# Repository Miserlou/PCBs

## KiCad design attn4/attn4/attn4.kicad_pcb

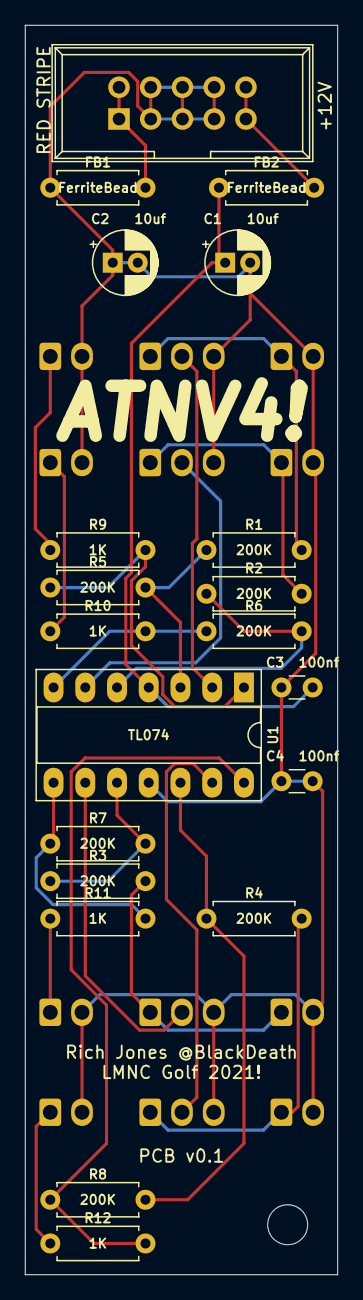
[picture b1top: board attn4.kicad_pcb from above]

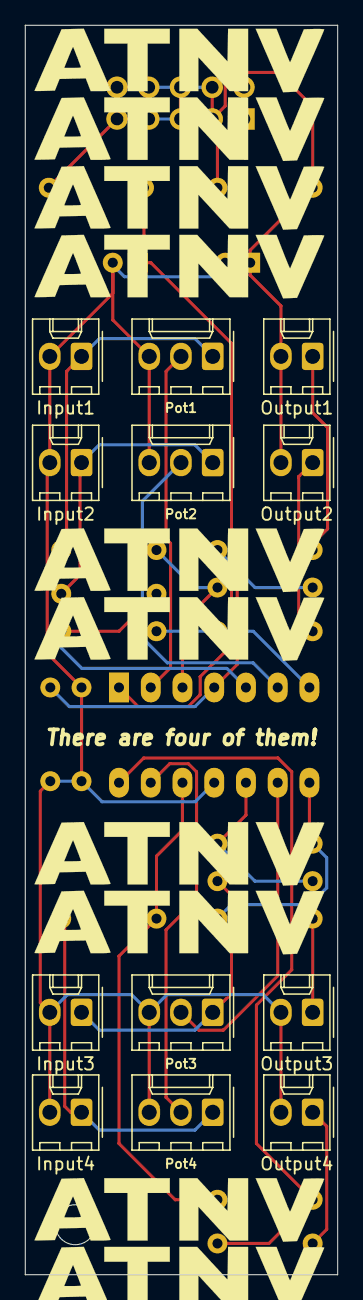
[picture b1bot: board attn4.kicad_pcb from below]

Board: 2 copper layers, 25.0 x 100.0 mm, 33 parts (12 on the bottom side), 24 nets.

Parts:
C1, C2: 10uf; CP_Radial_D5.0mm_P2.00mm
C3, C4: 100nf; C_Disc_D3.0mm_W1.6mm_P2.50mm
FB1, FB2: FerriteBead; R_Axial_DIN0207_L6.3mm_D2.5mm_P7.62mm_Horizontal
H1: MountingHole; MountingHole_3.2mm_M3
Input1: Input1; Molex_KK-254_AE-6410-02A_1x02_P2.54mm_Vertical
Input2: Input2; Molex_KK-254_AE-6410-02A_1x02_P2.54mm_Vertical
Input3: Input3; Molex_KK-254_AE-6410-02A_1x02_P2.54mm_Vertical
Input4: Input4; Molex_KK-254_AE-6410-02A_1x02_P2.54mm_Vertical
J5: Synth_power_2x5; Power_Header
Output1: Output1; Molex_KK-254_AE-6410-02A_1x02_P2.54mm_Vertical
Output2: Output2; Molex_KK-254_AE-6410-02A_1x02_P2.54mm_Vertical
Output3: Output3; Molex_KK-254_AE-6410-02A_1x02_P2.54mm_Vertical
Output4: Output4; Molex_KK-254_AE-6410-02A_1x02_P2.54mm_Vertical
Pot1, Pot2, Pot3, Pot4: 100K; Molex_KK-254_AE-6410-03A_1x03_P2.54mm_Vertical
R1, R2, R3, R4, R5, R6, R7, R8: 200K; R_Axial_DIN0207_L6.3mm_D2.5mm_P7.62mm_Horizontal
R9, R10, R11, R12: 1K; R_Axial_DIN0207_L6.3mm_D2.5mm_P7.62mm_Horizontal
U1: TL074; DIP-14_W7.62mm_Socket_LongPads

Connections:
GND: C1.2, C2.1, C2.2, C3.1, C4.1, C4.2, FB1.1, Input1.2, Input2.2, Input3.2, Input4.2, J5.3, J5.4, J5.5, J5.6, J5.7, J5.8, Output1.2, Output2.2, Output3.2, Output4.2, Pot1.3, Pot2.3, Pot3.3, Pot4.3, U1.11
unnamed: C1.1, C3.2, FB2.1, U1.4
unnamed: FB1.2, J5.1, J5.2
unnamed: FB2.2, J5.9, J5.10
unnamed: Input1.1, Pot1.1, R1.2
unnamed: Input2.1, Pot2.1, R2.2
unnamed: Input3.1, Pot3.1, R3.2
unnamed: Input4.1, Pot4.1, R4.2
unnamed: Output1.1, R9.1
unnamed: Output2.1, R10.1
unnamed: Output3.1, R11.1
unnamed: Output4.1, R12.1
unnamed: Pot1.2, U1.2
unnamed: Pot2.2, U1.6
unnamed: Pot3.2, U1.9
unnamed: Pot4.2, U1.13
unnamed: R1.1, R5.2, U1.3
unnamed: R2.1, R6.2, U1.5
unnamed: R3.1, R7.2, U1.10
unnamed: R4.1, R8.2, U1.12
unnamed: R5.1, R9.2, U1.1
unnamed: R6.1, R10.2, U1.7
unnamed: R7.1, R11.2, U1.8
unnamed: R8.1, R12.2, U1.14

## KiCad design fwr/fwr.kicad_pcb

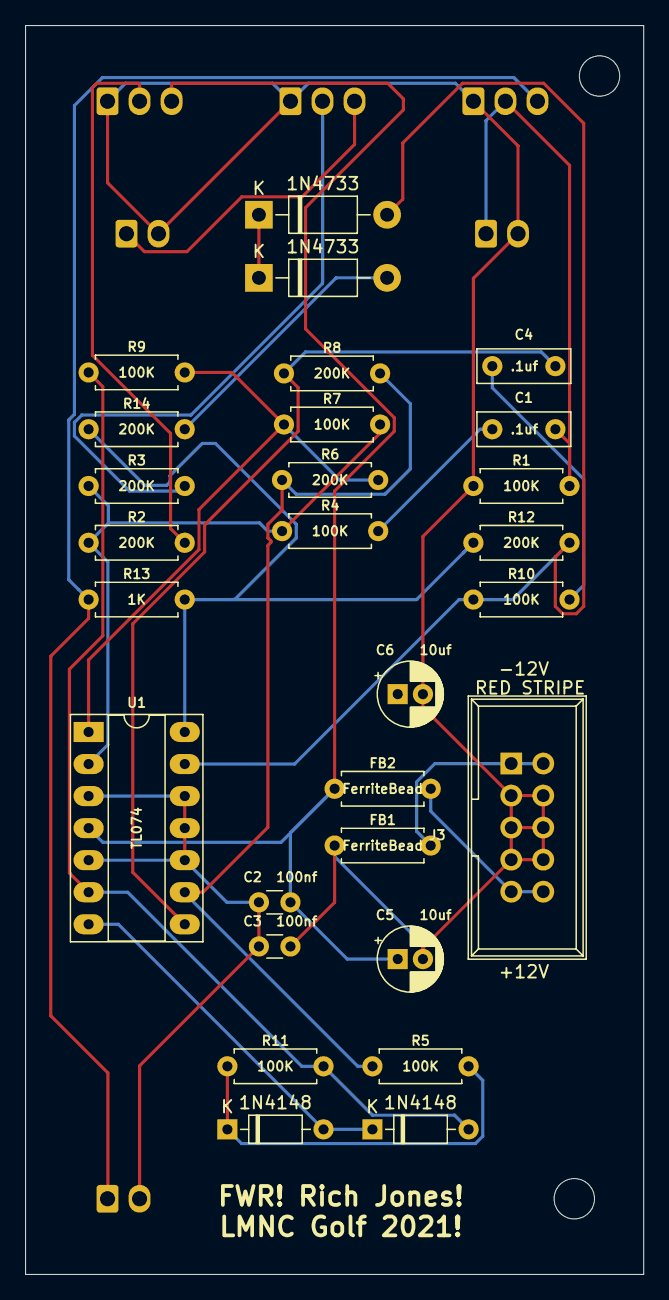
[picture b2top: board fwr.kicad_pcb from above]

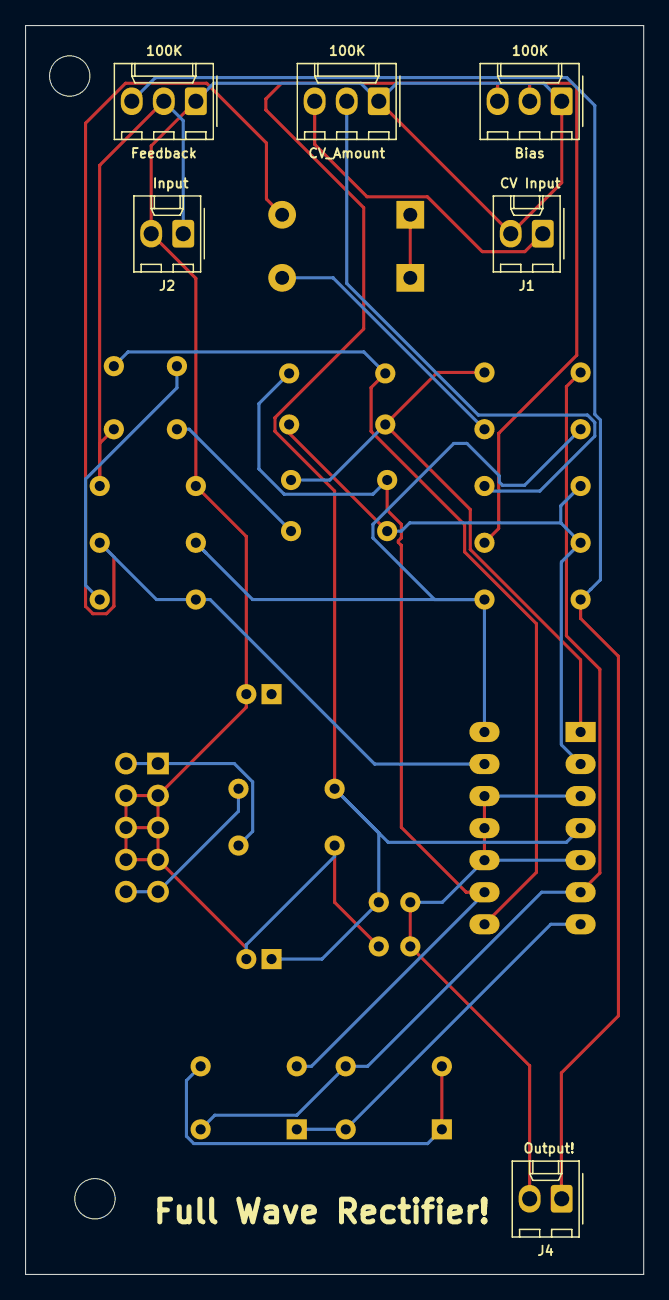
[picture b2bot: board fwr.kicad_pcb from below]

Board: 2 copper layers, 49.0 x 99.0 mm, 36 parts (6 on the bottom side), 22 nets.

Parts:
1N4148, 1N4148#2: 1N4148; D_DO-35_SOD27_P7.62mm_Horizontal
1N4733, 1N4733#2: 1N4733; D_DO-41_SOD81_P10.16mm_Horizontal
 : MountingHole; MountingHole_3.2mm_M3
Bias: 100K; Molex_KK-254_AE-6410-03A_1x03_P2.54mm_Vertical
C1, C4: .1uf; C_Rect_L7.2mm_W2.5mm_P5.00mm_FKS2_FKP2_MKS2_MKP2
C2, C3: 100nf; C_Disc_D3.0mm_W1.6mm_P2.50mm
C5, C6: 10uf; CP_Radial_D5.0mm_P2.00mm
CV_Amount: 100K; Molex_KK-254_AE-6410-03A_1x03_P2.54mm_Vertical
FB1, FB2: FerriteBead; R_Axial_DIN0207_L6.3mm_D2.5mm_P7.62mm_Horizontal
Feedback: 100K; Molex_KK-254_AE-6410-03A_1x03_P2.54mm_Vertical
H1: MountingHole; MountingHole_3.2mm_M3
J1: CV_Input; Molex_KK-254_AE-6410-02A_1x02_P2.54mm_Vertical
J2: Input; Molex_KK-254_AE-6410-02A_1x02_P2.54mm_Vertical
J3: Synth_power_2x5; Power_Header
J4: Output; Molex_KK-254_AE-6410-02A_1x02_P2.54mm_Vertical
R1, R4, R5, R7, R9, R10, R11: 100K; R_Axial_DIN0207_L6.3mm_D2.5mm_P7.62mm_Horizontal
R2, R3, R6, R8, R12, R14: 200K; R_Axial_DIN0207_L6.3mm_D2.5mm_P7.62mm_Horizontal
R13: 1K; R_Axial_DIN0207_L6.3mm_D2.5mm_P7.62mm_Horizontal
U1: TL074; DIP-14_W7.62mm_Socket_LongPads

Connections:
+12V: Bias.3, C2.2, C5.1, FB2.1, U1.4
-12V: Bias.1, C2.1, C3.1, C3.2, C5.2, C6.1, C6.2, CV_Amount.1, FB1.1, Feedback.1, J1.2, J2.2, J3.3, J3.4, J3.5, J3.6, J3.7, J3.8, J4.2, R1.1, U1.3, U1.5, U1.10, U1.11, U1.12
unnamed: Bias.2, R2.2
unnamed: C1.1, R4.2
unnamed: C1.2, Feedback.2, J2.1, R1.2
unnamed: C4.1, R10.2
unnamed: C4.2, R8.1, U1.8
unnamed: CV_Amount.2, R3.2
unnamed: CV_Amount.3, J1.1
unnamed: 1N4148.1, 1N4148#2.2, U1.7
unnamed: 1N4148.2, R9.1, R11.2, U1.6
unnamed: 1N4148#2.1, R5.2, R11.1
unnamed: 1N4733.1, 1N4733#2.1
unnamed: 1N4733.2, R10.1, R12.2, U1.13
unnamed: 1N4733#2.2, R14.2
unnamed: FB1.2, J3.1, J3.2
unnamed: FB2.2, J3.9, J3.10
unnamed: Feedback.3, J4.1, R13.1
unnamed: R2.1, R3.1, R4.1, R7.2, U1.2
unnamed: R5.1, R6.1, R8.2, U1.9
unnamed: R6.2, R7.1, R9.2, U1.1
unnamed: R12.1, R13.2, R14.1, U1.14

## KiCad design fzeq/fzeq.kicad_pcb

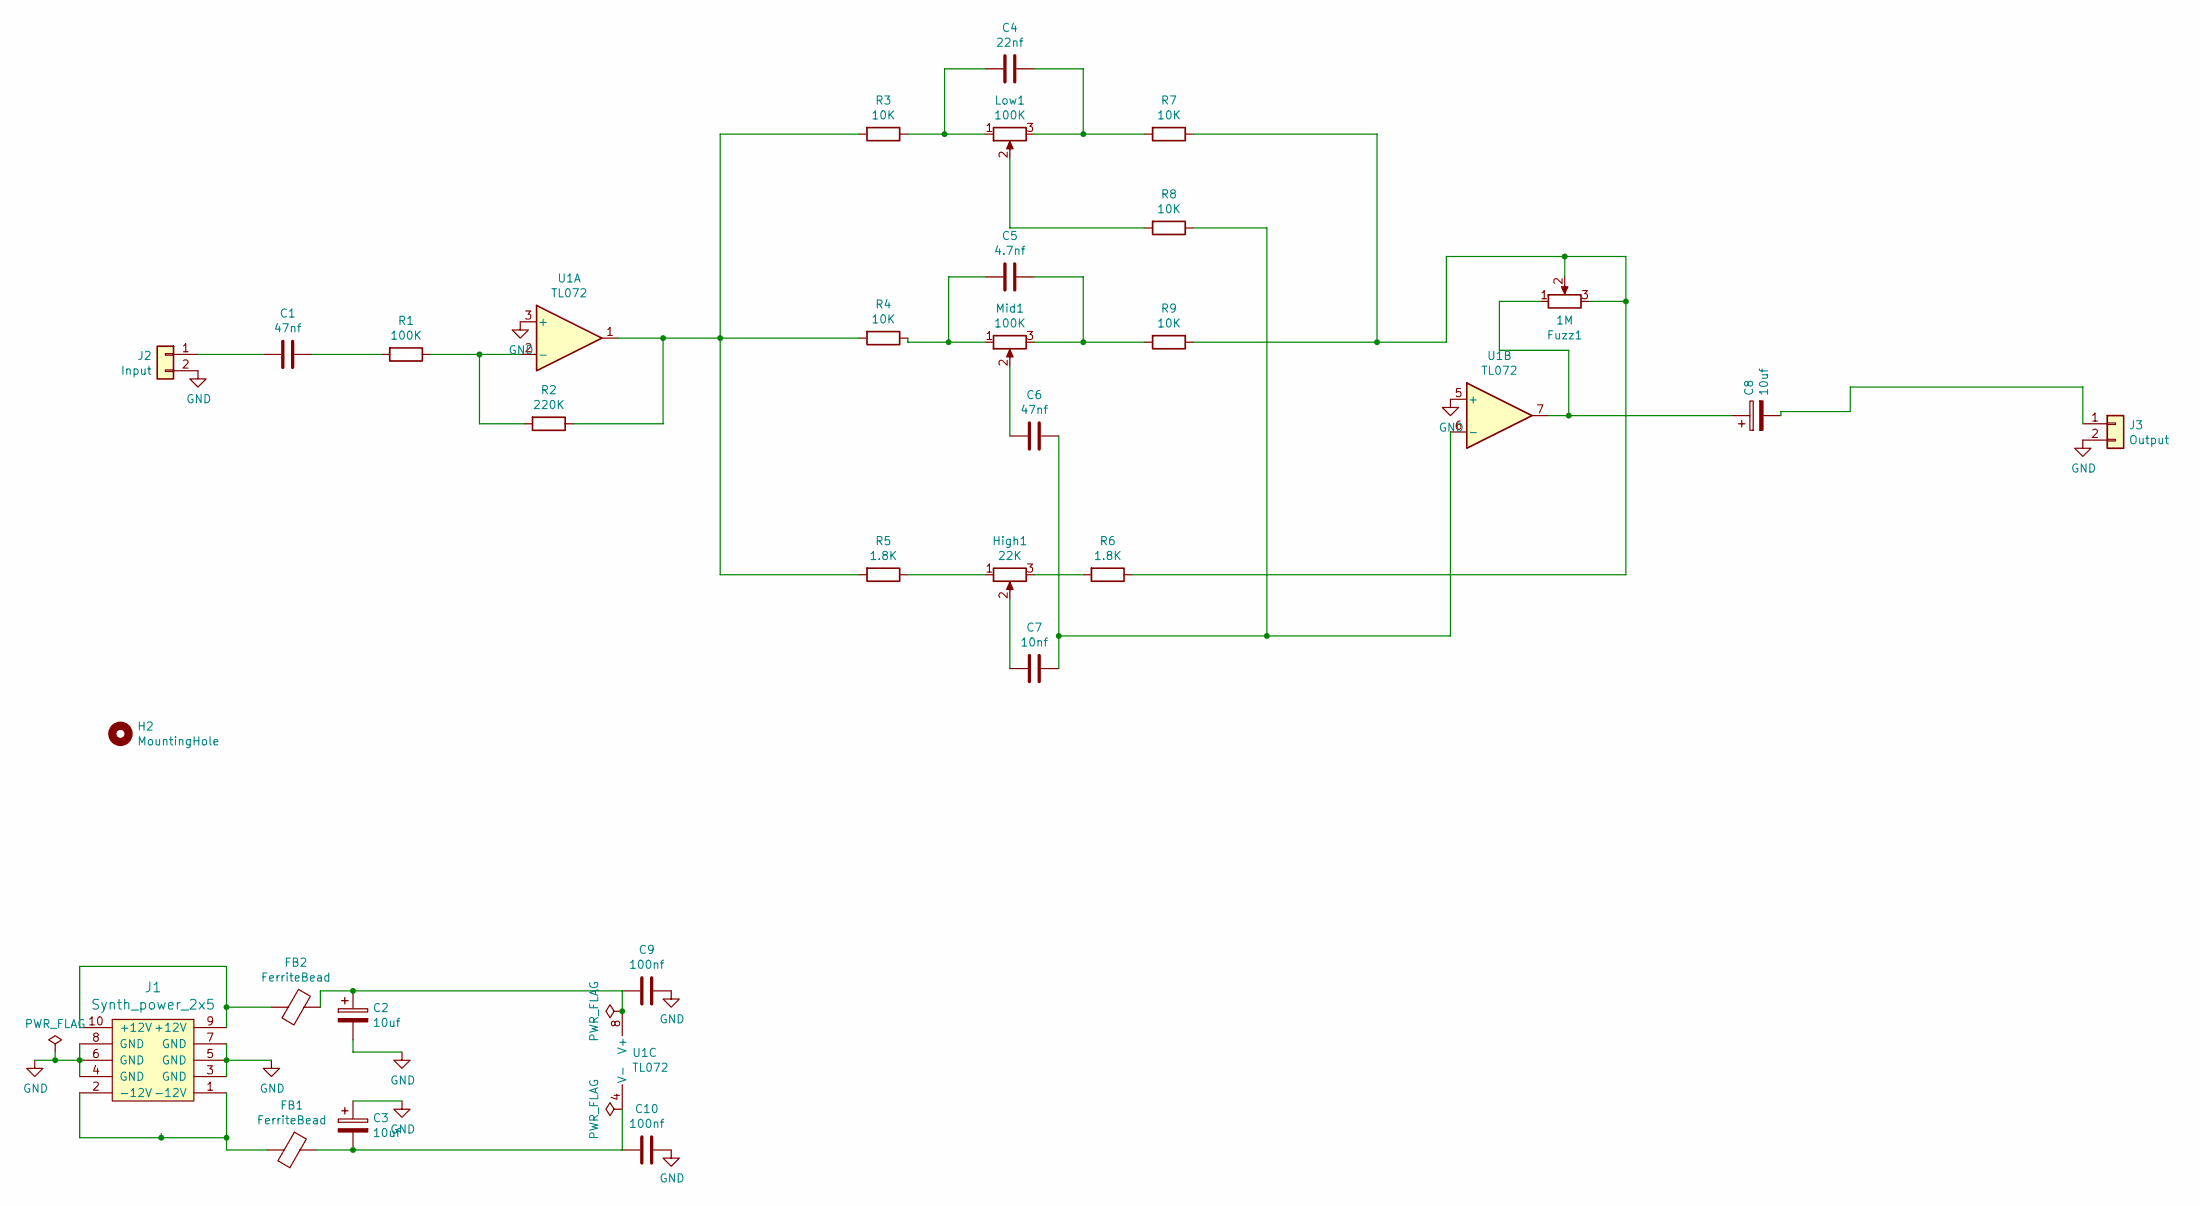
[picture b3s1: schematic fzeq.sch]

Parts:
C1, C6: 47nf; C_Disc_D3.0mm_W1.6mm_P2.50mm
C2, C3, C8: 10uf; CP_Radial_D5.0mm_P2.00mm
C4: 22nf; C_Disc_D3.0mm_W1.6mm_P2.50mm
C5: 4.7nf; C_Disc_D3.0mm_W1.6mm_P2.50mm
C7: 10nf; C_Disc_D3.0mm_W1.6mm_P2.50mm
C9, C10: 100nf; C_Disc_D3.0mm_W1.6mm_P2.50mm
FB1, FB2: FerriteBead; R_Axial_DIN0207_L6.3mm_D2.5mm_P7.62mm_Horizontal
Fuzz1: 1M; Molex_KK-254_AE-6410-03A_1x03_P2.54mm_Vertical
H2: MountingHole; MountingHole_3.2mm_M3
High1: 22K; Molex_KK-254_AE-6410-03A_1x03_P2.54mm_Vertical
J1: Synth_power_2x5; Power_Header
J2: Input; Molex_KK-254_AE-6410-02A_1x02_P2.54mm_Vertical
J3: Output; Molex_KK-254_AE-6410-02A_1x02_P2.54mm_Vertical
Low1: 100K; Molex_KK-254_AE-6410-03A_1x03_P2.54mm_Vertical
Mid1: 100K; Molex_KK-254_AE-6410-03A_1x03_P2.54mm_Vertical
R1: 100K; R_Axial_DIN0207_L6.3mm_D2.5mm_P7.62mm_Horizontal
R2: 220K; R_Axial_DIN0207_L6.3mm_D2.5mm_P7.62mm_Horizontal
R3, R4, R7, R8, R9: 10K; R_Axial_DIN0207_L6.3mm_D2.5mm_P7.62mm_Horizontal
R5, R6: 1.8K; R_Axial_DIN0207_L6.3mm_D2.5mm_P7.62mm_Horizontal
U1: TL072; DIP-8_W7.62mm_Socket_LongPads

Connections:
GND: C2.2, C3.1, C9.1, C10.1, J1.3 (GND), J1.4 (GND), J1.5 (GND), J1.6 (GND), J1.7 (GND), J1.8 (GND), J2.2, J3.2, U1.3 (+), U1.5 (+)
unnamed: C1.1, R1.2
unnamed: C1.2, J2.1
unnamed: C2.1, C9.2, FB2.1, U1.8 (V+)
unnamed: C4.1, Low1.3, R7.2
unnamed: C4.2, Low1.1, R3.1
unnamed: C5.1, Mid1.3, R9.2
unnamed: C5.2, Mid1.1, R4.1
unnamed: C6.1, C7.1, R8.1, U1.6 (-)
unnamed: C6.2, Mid1.2
unnamed: C7.2, High1.2
unnamed: C8.1, Fuzz1.1, U1.7
unnamed: C8.2, J3.1
unnamed: C3.2, C10.2, FB1.1, U1.4 (V-)
unnamed: FB1.2, J1.1 (-12V), J1.2 (-12V)
unnamed: FB2.2, J1.9 (+12V), J1.10 (+12V)
unnamed: Fuzz1.2, Fuzz1.3, R6.1, R7.1, R9.1
unnamed: High1.1, R5.1
unnamed: High1.3, R6.2
unnamed: Low1.2, R8.2
unnamed: R1.1, R2.2, U1.2 (-)
unnamed: R2.1, R3.2, R4.2, R5.2, U1.1

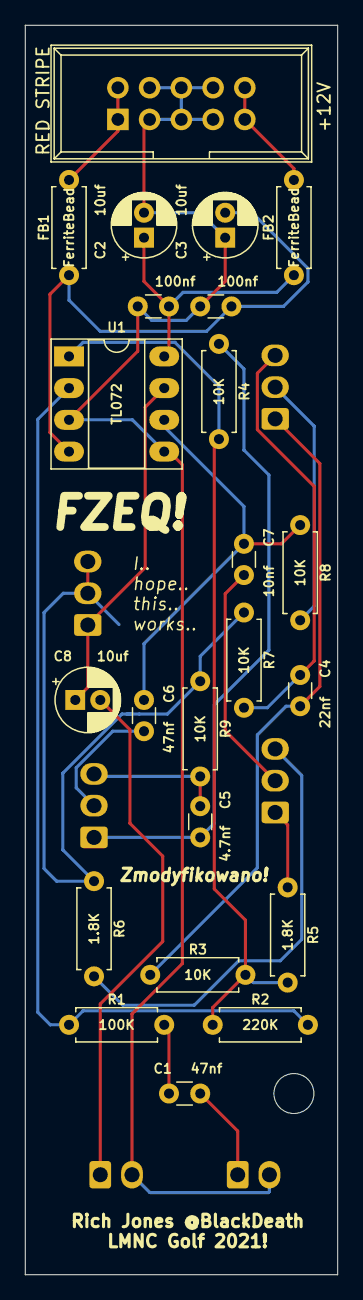
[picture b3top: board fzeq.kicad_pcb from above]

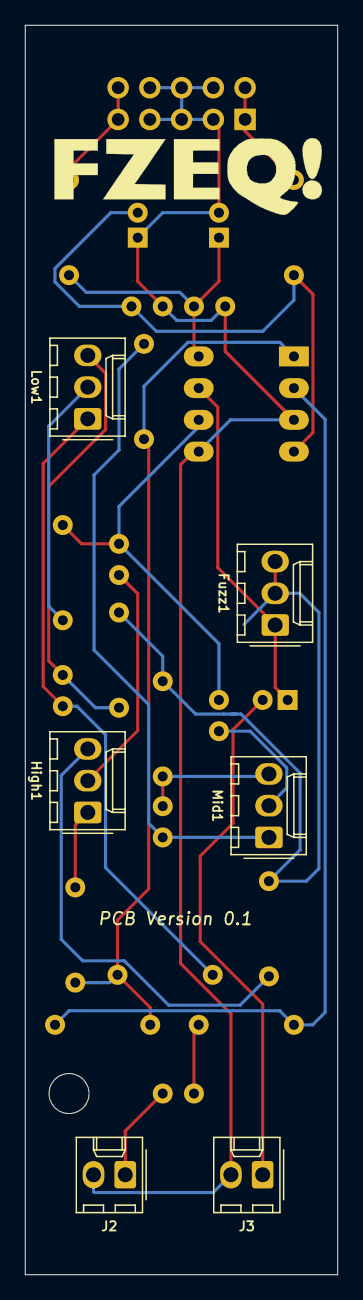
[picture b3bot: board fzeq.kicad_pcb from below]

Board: 2 copper layers, 25.0 x 100.0 mm, 30 parts (6 on the bottom side), 22 nets.

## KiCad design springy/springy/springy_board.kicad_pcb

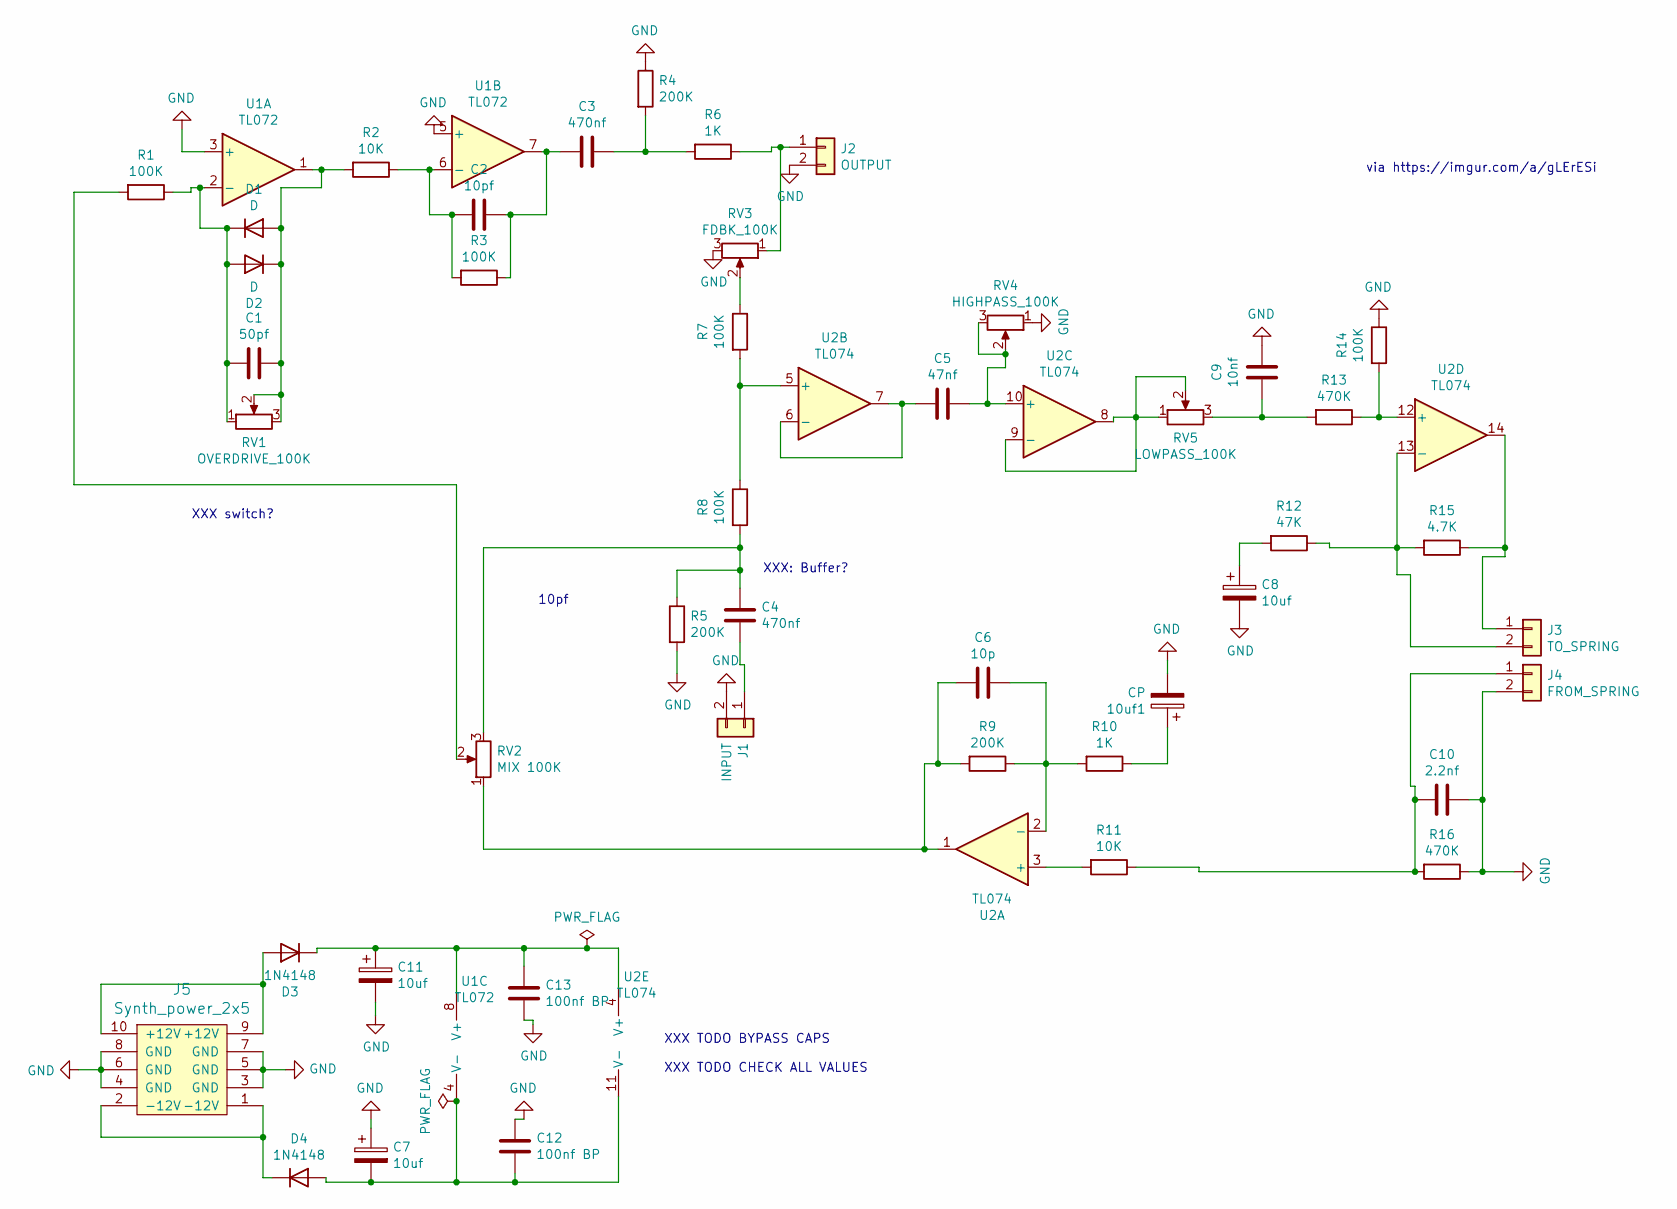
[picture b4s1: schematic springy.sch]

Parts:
10uf1: CP; CP_Radial_D6.3mm_P2.50mm
C1: 50pf; C_Disc_D3.0mm_W1.6mm_P2.50mm
C2: 10pf; C_Disc_D3.0mm_W1.6mm_P2.50mm
C3, C4: 470nf; C_Disc_D3.0mm_W1.6mm_P2.50mm
C5: 47nf; C_Disc_D3.0mm_W1.6mm_P2.50mm
C6: 10p; C_Disc_D3.0mm_W1.6mm_P2.50mm
C7, C8, C11: 10uf; CP_Radial_D6.3mm_P2.50mm
C9: 10nf; C_Disc_D3.0mm_W1.6mm_P2.50mm
C10: 2.2nf; C_Disc_D3.0mm_W1.6mm_P2.50mm
C12, C13: 100nf BP; C_Disc_D3.0mm_W1.6mm_P2.50mm
D1, D2: D; D_DO-41_SOD81_P7.62mm_Horizontal
D3, D4: 1N4148; D_DO-35_SOD27_P7.62mm_Horizontal
J1: INPUT; Molex_KK-254_AE-6410-02A_1x02_P2.54mm_Vertical
J2: OUTPUT; Molex_KK-254_AE-6410-02A_1x02_P2.54mm_Vertical
J3: TO_SPRING; Molex_KK-254_AE-6410-02A_1x02_P2.54mm_Vertical
J4: FROM_SPRING; Molex_KK-254_AE-6410-02A_1x02_P2.54mm_Vertical
J5: Synth_power_2x5; Power_Header
R1, R3, R7, R8, R14: 100K; R_Axial_DIN0207_L6.3mm_D2.5mm_P10.16mm_Horizontal
R2, R11: 10K; R_Axial_DIN0207_L6.3mm_D2.5mm_P10.16mm_Horizontal
R4, R5, R9: 200K; R_Axial_DIN0207_L6.3mm_D2.5mm_P10.16mm_Horizontal
R6, R10: 1K; R_Axial_DIN0207_L6.3mm_D2.5mm_P10.16mm_Horizontal
R12: 47K; R_Axial_DIN0207_L6.3mm_D2.5mm_P10.16mm_Horizontal
R13, R16: 470K; R_Axial_DIN0207_L6.3mm_D2.5mm_P10.16mm_Horizontal
R15: 4.7K; R_Axial_DIN0207_L6.3mm_D2.5mm_P10.16mm_Horizontal
RV1: OVERDRIVE_100K; Potentiometer_Alpha_RD901F-40-00D_Single_Vertical_CircularH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
RV2: MIX 100K; Potentiometer_Alpha_RD901F-40-00D_Single_Vertical_CircularH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
RV3: FDBK_100K; Potentiometer_Alpha_RD901F-40-00D_Single_Vertical_CircularH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
RV4: HIGHPASS_100K; Potentiometer_Alpha_RD901F-40-00D_Single_Vertical_CircularH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
RV5: LOWPASS_100K; Potentiometer_Alpha_RD901F-40-00D_Single_Vertical_CircularH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
U1: TL072; DIP-8_W7.62mm_Socket_LongPads
U2: TL074; DIP-16_W7.62mm_Socket_LongPads

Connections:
GND: 10uf1.2, C7.1, C8.2, C9.2, C10.2, C11.2, C12.1, C13.2, J1.2, J2.2, J4.2, J5.3 (GND), J5.4 (GND), J5.5 (GND), J5.6 (GND), J5.7 (GND), J5.8 (GND), R4.1, R5.2, R14.1, R16.1, RV3.3, RV4.1, U1.3 (+), U1.5 (+); also elsewhere on the board
unnamed: 10uf1.1, R10.1
unnamed: C1.1, D1.1 (K), D2.2 (A), R1.1, RV1.1, U1.2 (-)
unnamed: C1.2, D1.2 (A), D2.1 (K), R2.2, RV1.2, RV1.3, U1.1
unnamed: C2.1, R2.1, R3.2, U1.6 (-)
unnamed: C2.2, C3.1, R3.1, U1.7
unnamed: C3.2, R4.2, R6.2
unnamed: C4.1, R5.1, R8.2, RV2.3
unnamed 8: C4.2, J1.1; also elsewhere on the board
unnamed: C5.1, U2.6 (-), U2.7
unnamed: C5.2, RV4.2, RV4.3, U2.10 (+)
unnamed: C6.1, R9.2, RV2.1, U2.1
unnamed: C6.2, R9.1, R10.2, U2.2 (-)
unnamed: C8.1, R12.2
unnamed: C9.1, R13.2, RV5.3
unnamed 15: C10.1, J4.1, R11.1, R16.2; also elsewhere on the board
unnamed: C11.1, C13.1, D3.1 (K), U1.8 (V+), U2.4 (V+)
unnamed: C7.2, C12.2, D4.2 (A), U1.4 (V-), U2.11 (V-)
unnamed: D3.2 (A), J5.9 (+12V), J5.10 (+12V)
unnamed: D4.1 (K), J5.1 (-12V), J5.2 (-12V)
unnamed 20: J2.1, R6.1, RV3.1; also elsewhere on the board
unnamed 21: J3.1, R15.1, U2.14; also elsewhere on the board
unnamed 22: J3.2, R12.1, R15.2, U2.13 (-); also elsewhere on the board
unnamed: R1.2, RV2.2
unnamed: R7.1, RV3.2
unnamed: R7.2, R8.1, U2.5 (+)
unnamed: R11.2, U2.3 (+)
unnamed: R13.1, R14.2, U2.12 (+)
unnamed: RV5.1, RV5.2, U2.8, U2.9 (-)

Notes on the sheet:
XXX: Buffer?
via https://imgur.com/a/gLErESi
10pf
XXX TODO BYPASS CAPS XXX TODO CHECK ALL VALUES
XXX switch?

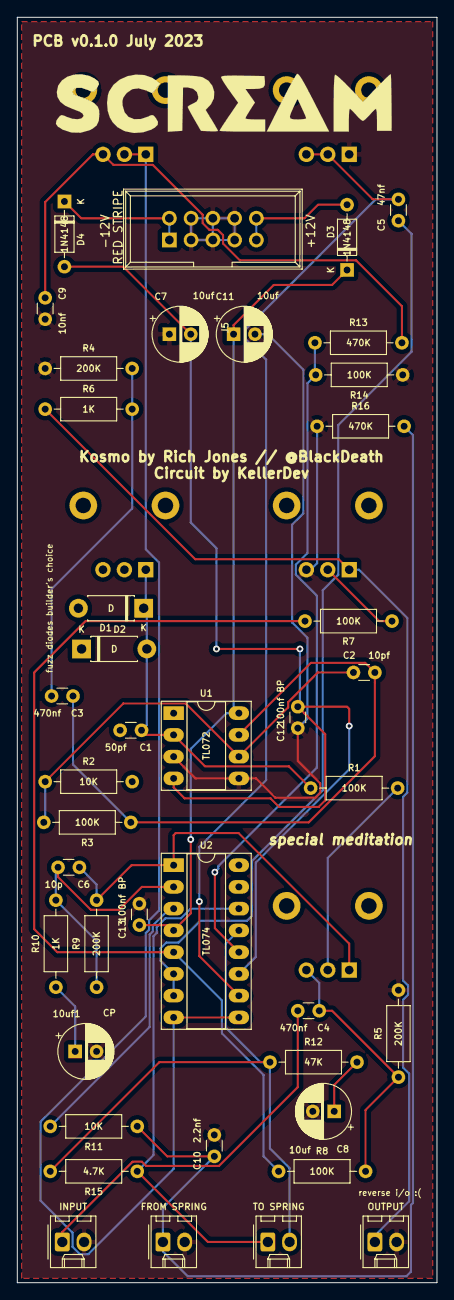
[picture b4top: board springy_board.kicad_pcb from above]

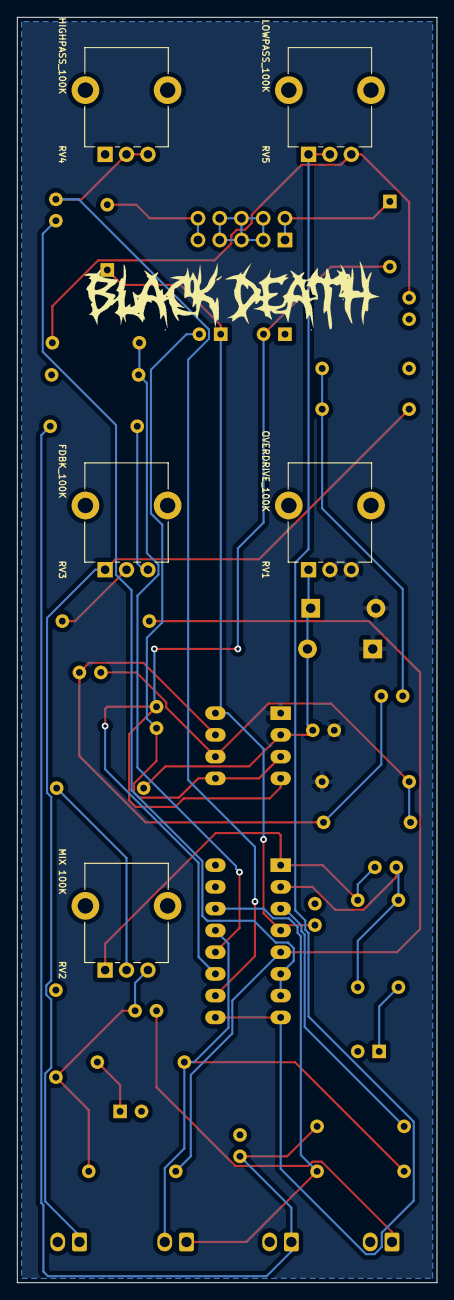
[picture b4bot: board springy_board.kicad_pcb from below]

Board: 2 copper layers, 49.0 x 147.8 mm, 46 parts (5 on the bottom side), 29 nets.

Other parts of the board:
FROM SPRING: FROM_SPRING; Molex_KK-254_AE-6410-02A_1x02_P2.54mm_Vertical
INPUT: INPUT; Molex_KK-254_AE-6410-02A_1x02_P2.54mm_Vertical
OUTPUT: OUTPUT; Molex_KK-254_AE-6410-02A_1x02_P2.54mm_Vertical
TO SPRING: TO_SPRING; Molex_KK-254_AE-6410-02A_1x02_P2.54mm_Vertical

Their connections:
GND: FROM SPRING.2, INPUT.2, OUTPUT.2; also elsewhere on the board
unnamed 8: INPUT.1; also elsewhere on the board
unnamed 15: FROM SPRING.1; also elsewhere on the board
unnamed 20: OUTPUT.1; also elsewhere on the board
unnamed 21: TO SPRING.1; also elsewhere on the board
unnamed 22: TO SPRING.2; also elsewhere on the board
